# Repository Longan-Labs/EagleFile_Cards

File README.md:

# EagleFile_Cards
Eagle for All the Cards

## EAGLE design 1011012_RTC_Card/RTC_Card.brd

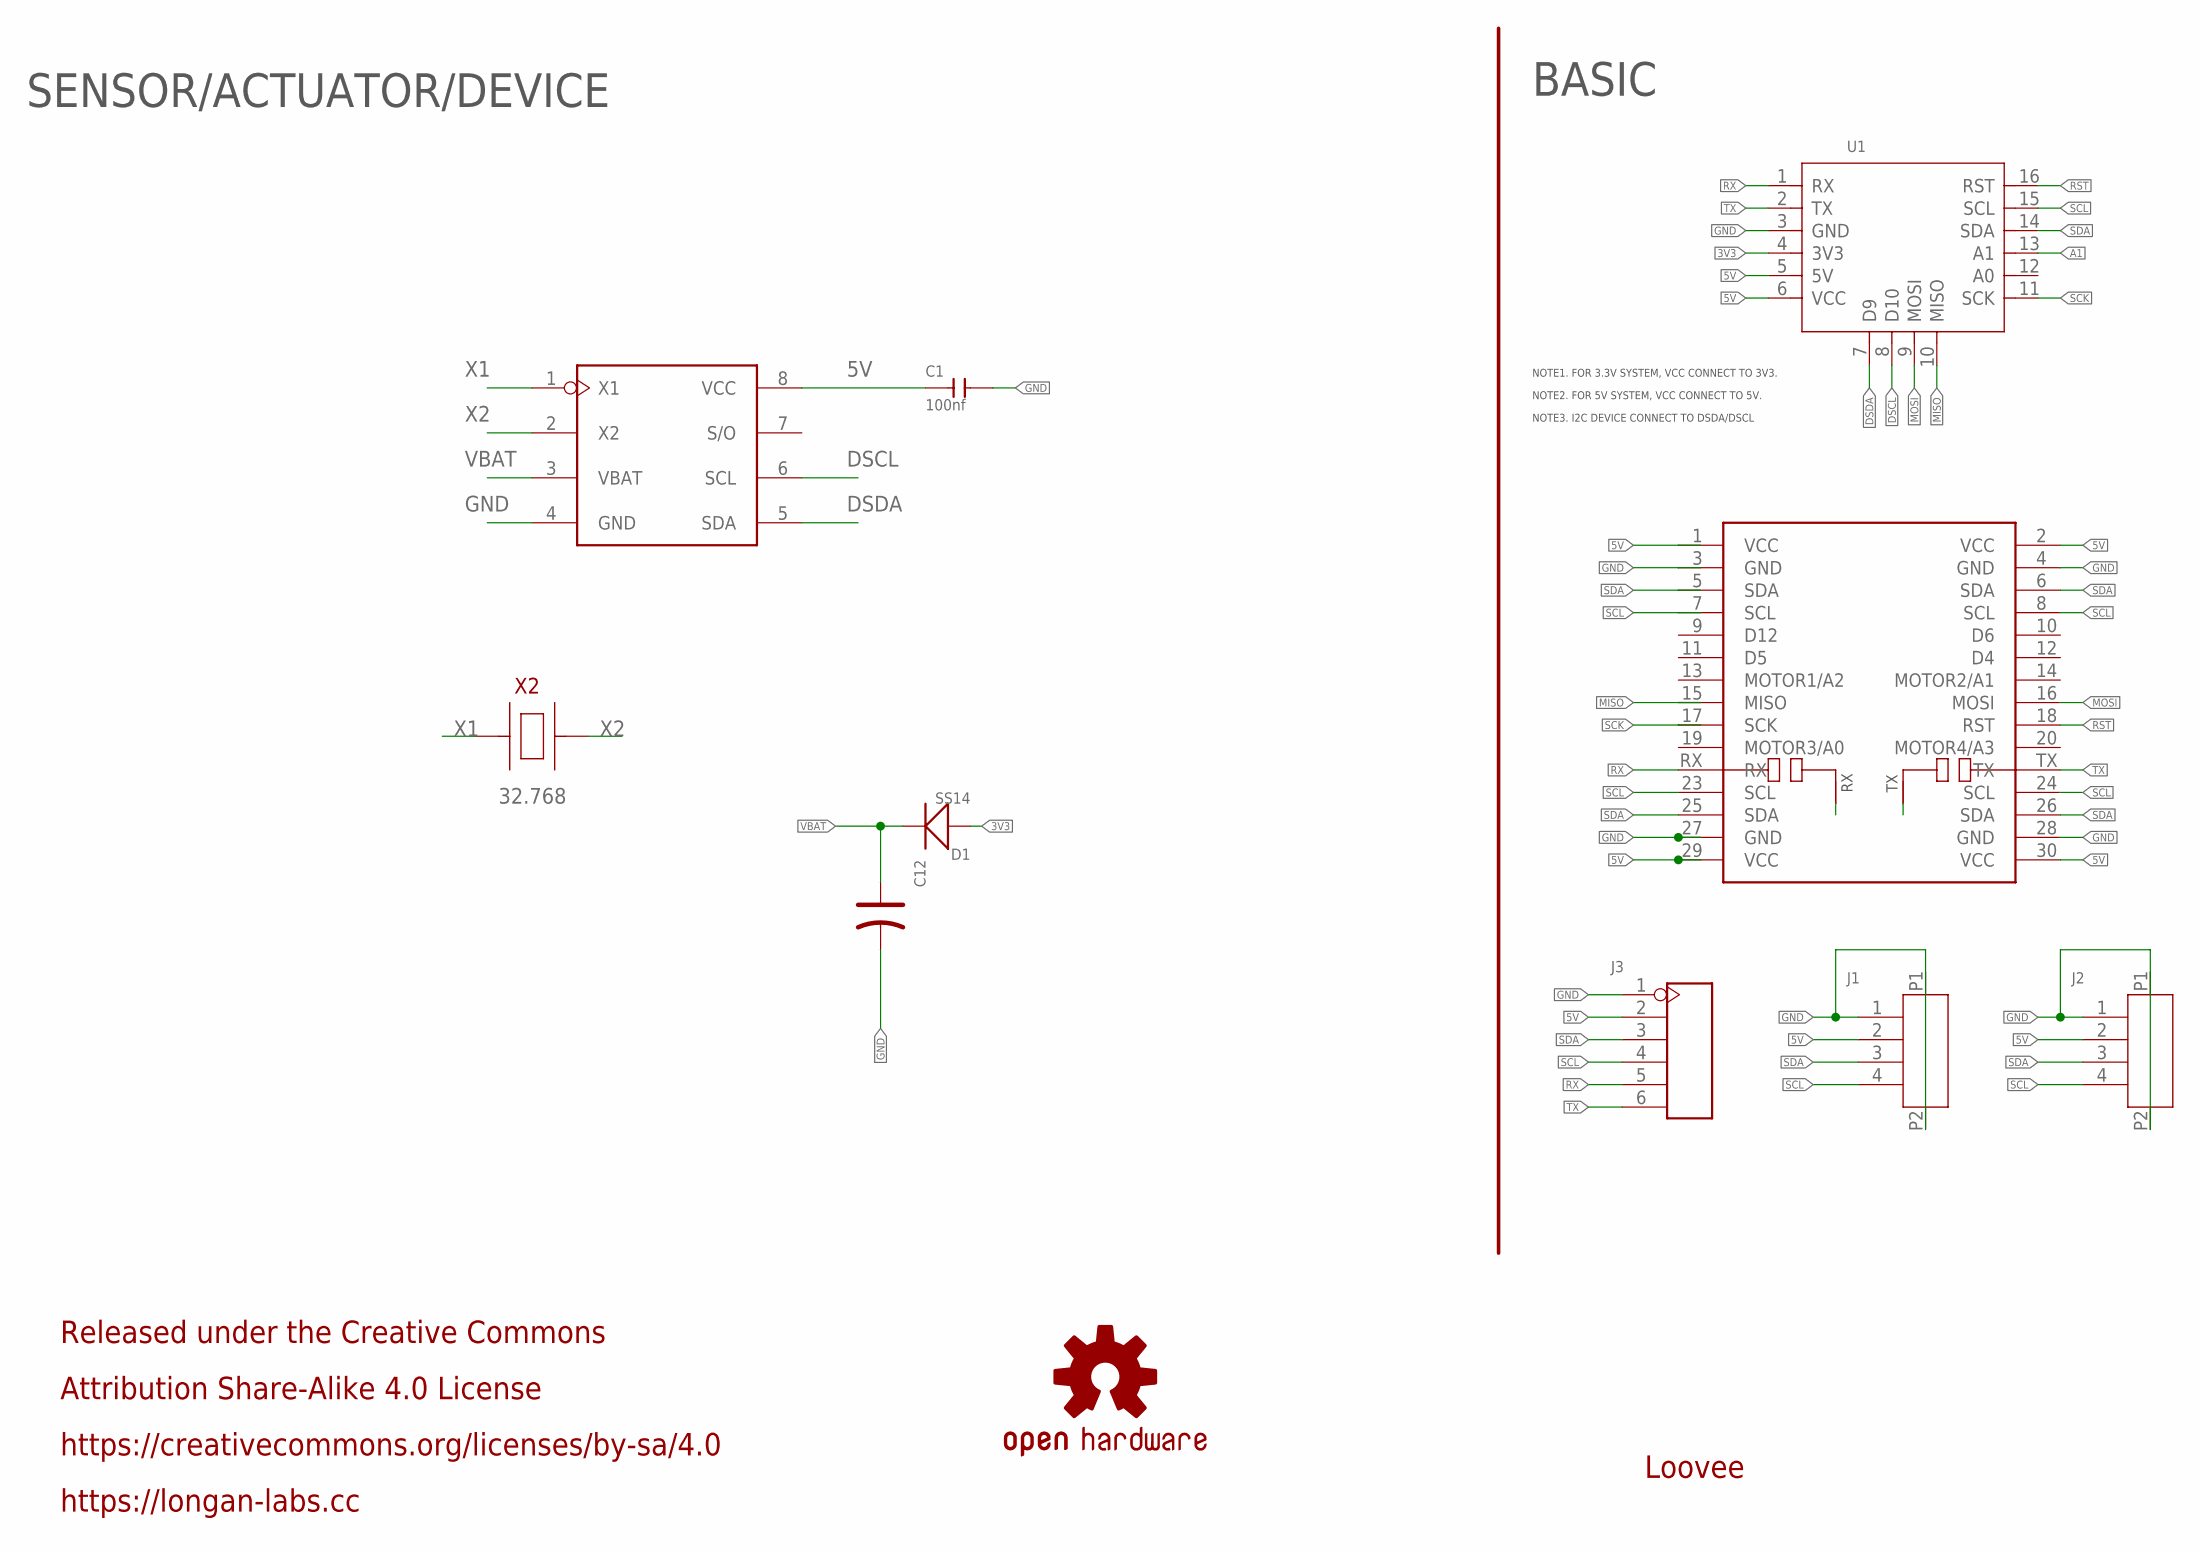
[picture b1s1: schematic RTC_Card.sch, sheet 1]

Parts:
C1: 100nf; C0603
C12: CAP-POLAR-CS-ME-414TA; SC-2P-D4.8MM
D1: SS14; DO-214AC
J1, J2: HEADER-4P-1.0; 4P-1.0-90D
J3: HEADER-6P-55/35MIL; H6-2.54
LOGO2: OSHW-LOGOS; OSHW-LOGO-S
MOUDLE2: MOUDLE-CARDS-UART'BOARD'; MOUDLE-2X15P-UART
U1: MOUDLE-CARDS; 16P-2.0-CARDS
U2: DS1307; SO08
X2: 32768; 2P-3215

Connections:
3V3: D1.1 (+), U1.4 (3V3)
5V: C1.1, J1.2, J2.2, J3.2, MOUDLE2.1 (VCC), MOUDLE2.2 (VCC), MOUDLE2.29 (VCC), MOUDLE2.30 (VCC), U1.5 (5V), U1.6 (VCC), U2.8 (VCC)
A1: U1.13 (A1)
DSCL: U1.8 (D10), U2.6 (SCL)
DSDA: U1.7 (D9), U2.5 (SDA)
GND: C1.2, C12.2 (-), J1.1, J1.P1, J1.P2, J2.1, J2.P1, J2.P2, J3.1, MOUDLE2.3 (GND), MOUDLE2.4 (GND), MOUDLE2.27 (GND), MOUDLE2.28 (GND), U1.3 (GND), U2.4 (GND)
MISO: MOUDLE2.15 (MISO), U1.10 (MISO)
MOSI: MOUDLE2.16 (MOSI), U1.9 (MOSI)
unnamed: MOUDLE2.RX/N1 (RX/N), MOUDLE2.RX/N2 (RX/N)
unnamed: MOUDLE2.TX/N1 (TX/N), MOUDLE2.TX/N2 (TX/N)
RST: MOUDLE2.18 (RST), U1.16 (RST)
RX: J3.5, MOUDLE2.RX, U1.1 (RX)
SCK: MOUDLE2.17 (SCK), U1.11 (SCK)
SCL: J1.4, J2.4, J3.4, MOUDLE2.7 (SCL), MOUDLE2.8 (SCL), MOUDLE2.23 (SCL), MOUDLE2.24 (SCL), U1.15 (SCL)
SDA: J1.3, J2.3, J3.3, MOUDLE2.5 (SDA), MOUDLE2.6 (SDA), MOUDLE2.25 (SDA), MOUDLE2.26 (SDA), U1.14 (SDA)
TX: J3.6, MOUDLE2.TX, U1.2 (TX)
VBAT: C12.1 (+), D1.2 (-), U2.3 (VBAT)
X1: U2.1 (X1), X2.X1
X2: U2.2 (X2), X2.X2

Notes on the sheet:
BASIC
Loovee
NOTE1. FOR 3.3V SYSTEM, VCC CONNECT TO 3V3.
NOTE2. FOR 5V SYSTEM, VCC CONNECT TO 5V.
NOTE3. I2C DEVICE CONNECT TO DSDA/DSCL
SENSOR/ACTUATOR/DEVICE
Released under the Creative Commons
Attribution Share-Alike 4.0 License
https://creativecommons.org/licenses/by-sa/4.0
https://longan-labs.cc
32.768

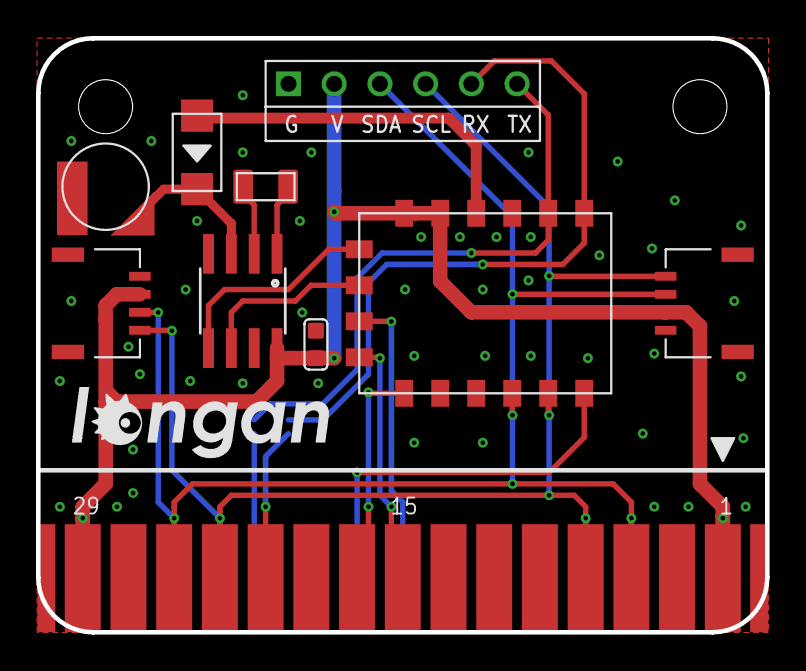
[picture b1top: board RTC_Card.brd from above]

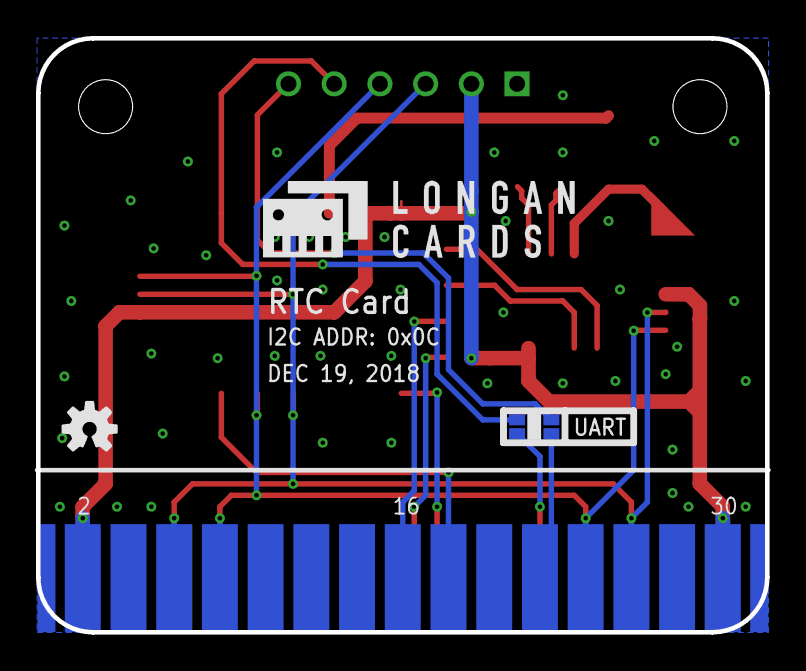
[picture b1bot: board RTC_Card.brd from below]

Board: 2 copper layers, 40.5 x 33.0 mm, 13 parts (2 on the bottom side), 18 nets.

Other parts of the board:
U$1: LONGAN-CARDS-MIDDLE
U$2: LONGAN-SILK-SMALLER

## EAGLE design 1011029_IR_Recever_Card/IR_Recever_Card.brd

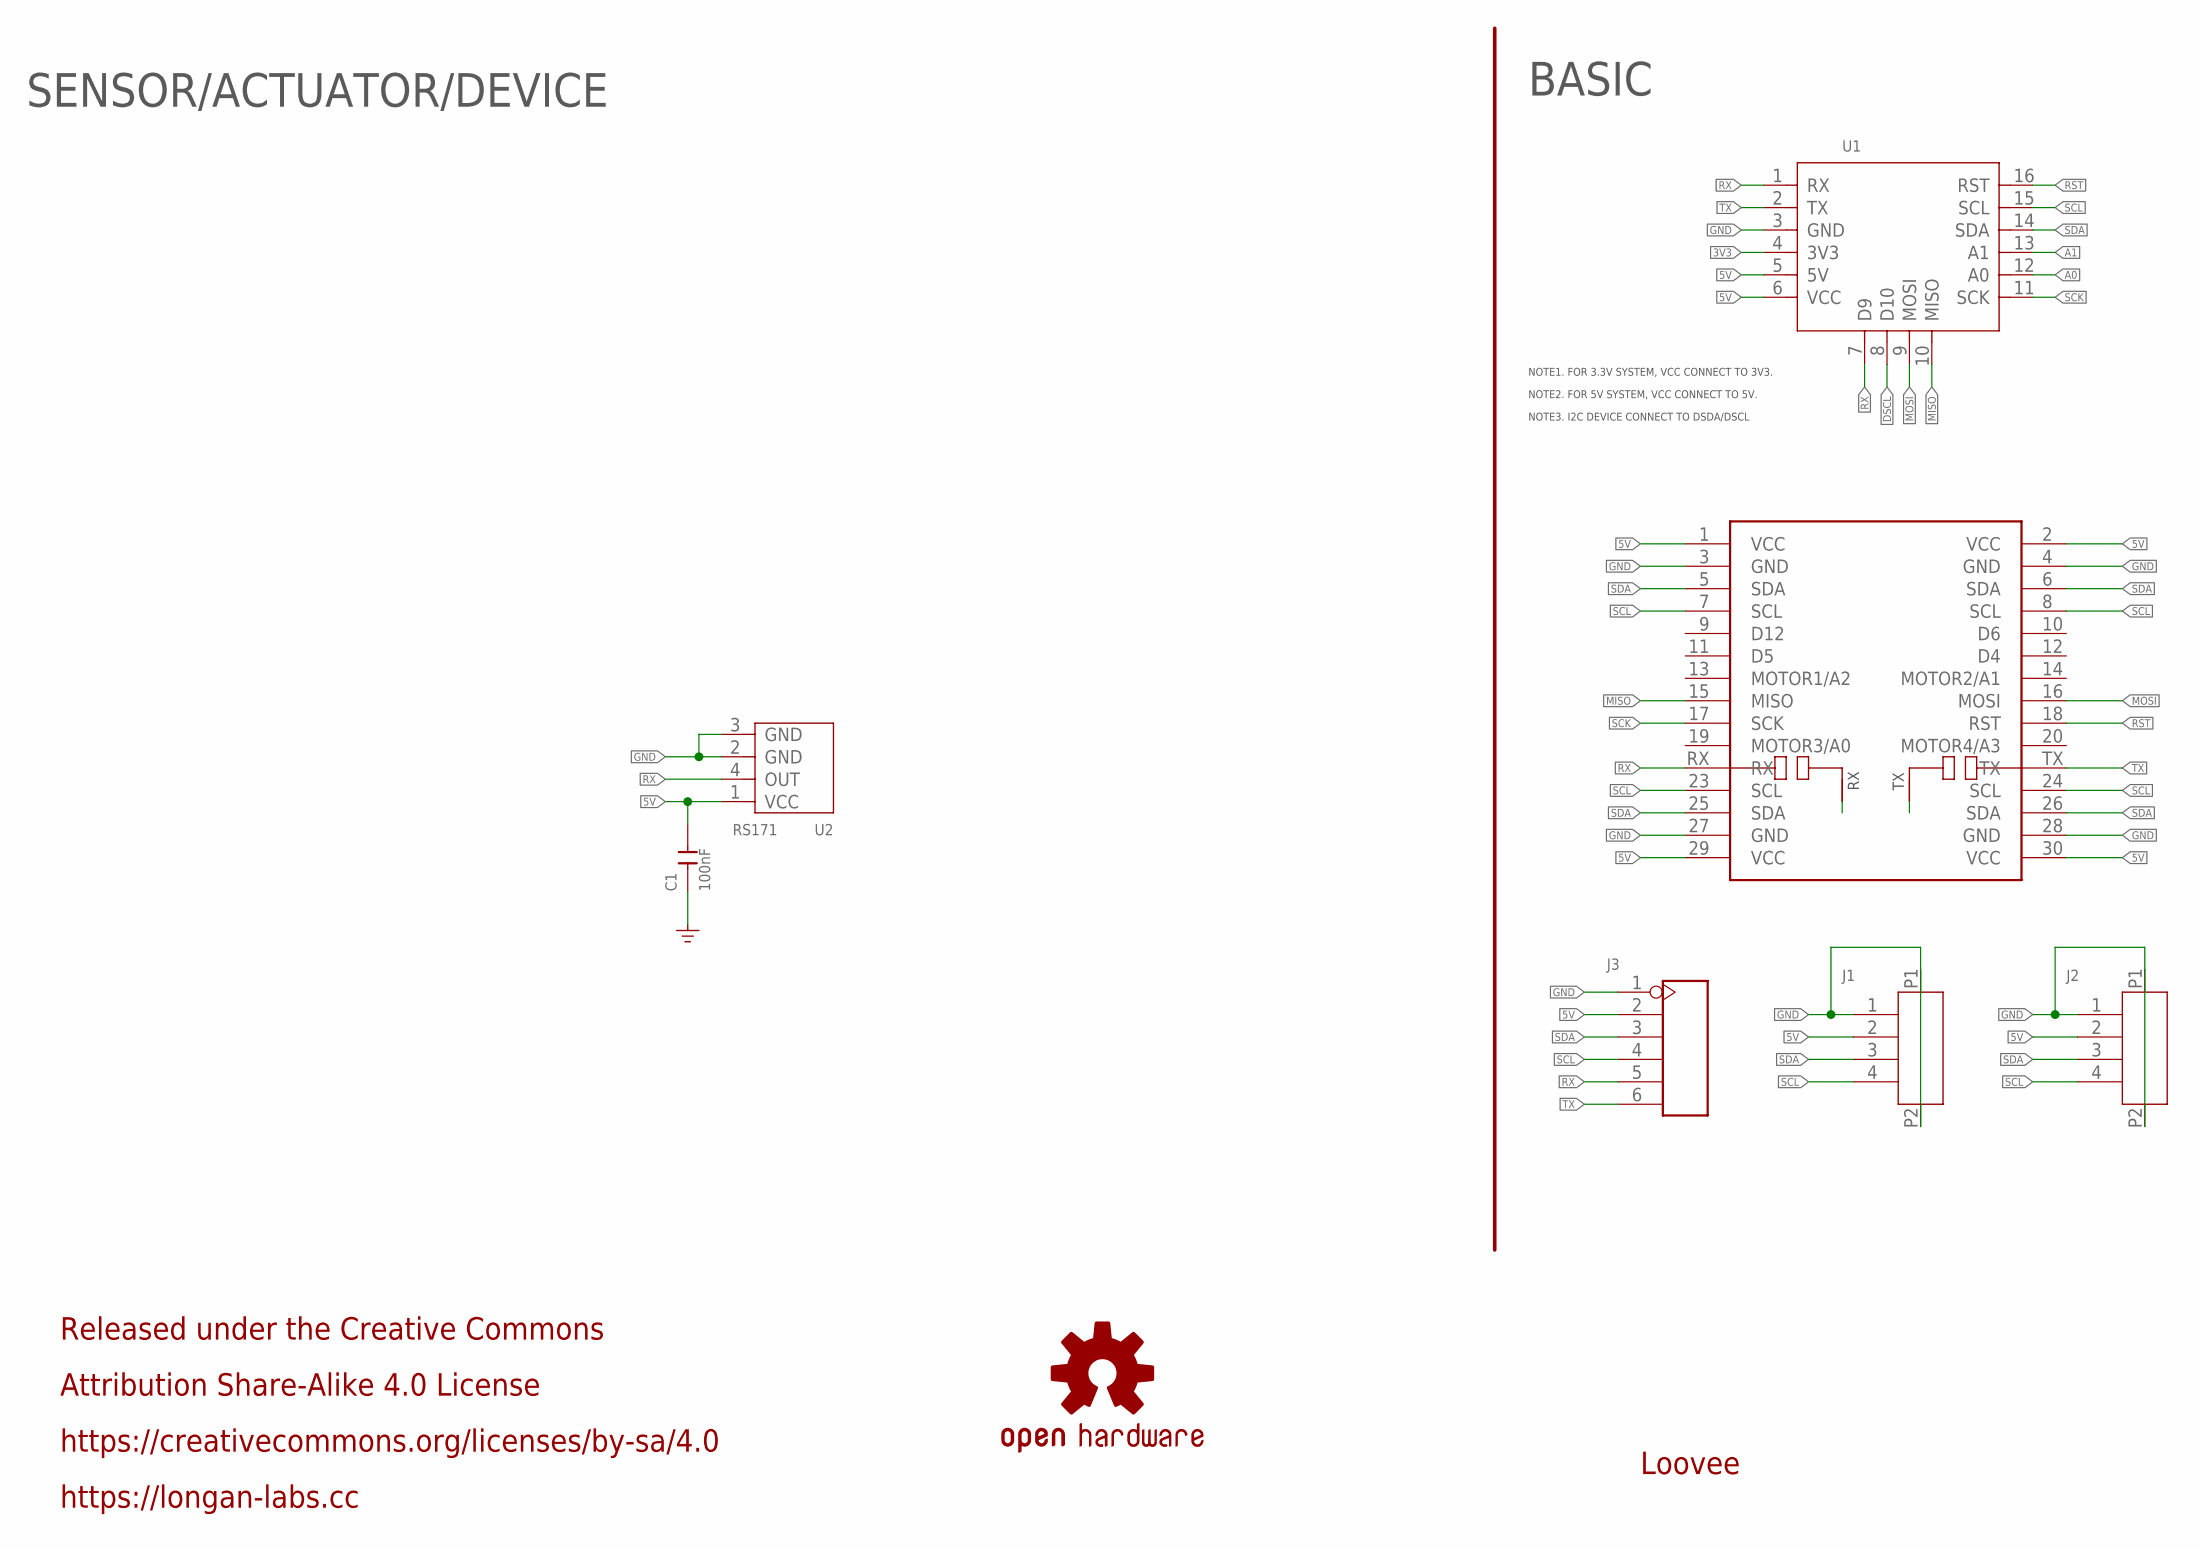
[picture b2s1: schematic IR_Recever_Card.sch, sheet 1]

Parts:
C1: 100nF; C0603
J1, J2: HEADER-4P-1.0; 4P-1.0-90D
J3: HEADER-6P-55/35MIL; H6-2.54
LOGO2: OSHW-LOGOS; OSHW-LOGO-S
MOUDLE1: MOUDLE-CARDS-UART'BOARD'; MOUDLE-2X15P-UART
U1: MOUDLE-CARDS; 16P-2.0-CARDS
U2: RS171; 4P-SMD-L7.6*W5.75MM

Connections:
3V3: U1.4 (3V3)
5V: C1.2, J1.2, J2.2, J3.2, MOUDLE1.1 (VCC), MOUDLE1.2 (VCC), MOUDLE1.29 (VCC), MOUDLE1.30 (VCC), U1.5 (5V), U1.6 (VCC), U2.1 (VCC)
A0: U1.12 (A0)
A1: U1.13 (A1)
DSCL: U1.8 (D10)
GND: C1.1, J1.1, J1.P1, J1.P2, J2.1, J2.P1, J2.P2, J3.1, MOUDLE1.3 (GND), MOUDLE1.4 (GND), MOUDLE1.27 (GND), MOUDLE1.28 (GND), U1.3 (GND), U2.2 (GND), U2.3 (GND)
MISO: MOUDLE1.15 (MISO), U1.10 (MISO)
MOSI: MOUDLE1.16 (MOSI), U1.9 (MOSI)
unnamed: MOUDLE1.RX/N1 (RX/N), MOUDLE1.RX/N2 (RX/N)
unnamed: MOUDLE1.TX/N1 (TX/N), MOUDLE1.TX/N2 (TX/N)
RST: MOUDLE1.18 (RST), U1.16 (RST)
RX: J3.5, MOUDLE1.RX, U1.1 (RX), U1.7 (D9), U2.4 (OUT)
SCK: MOUDLE1.17 (SCK), U1.11 (SCK)
SCL: J1.4, J2.4, J3.4, MOUDLE1.7 (SCL), MOUDLE1.8 (SCL), MOUDLE1.23 (SCL), MOUDLE1.24 (SCL), U1.15 (SCL)
SDA: J1.3, J2.3, J3.3, MOUDLE1.5 (SDA), MOUDLE1.6 (SDA), MOUDLE1.25 (SDA), MOUDLE1.26 (SDA), U1.14 (SDA)
TX: J3.6, MOUDLE1.TX, U1.2 (TX)

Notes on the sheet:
BASIC
Loovee
NOTE1. FOR 3.3V SYSTEM, VCC CONNECT TO 3V3.
NOTE2. FOR 5V SYSTEM, VCC CONNECT TO 5V.
NOTE3. I2C DEVICE CONNECT TO DSDA/DSCL
SENSOR/ACTUATOR/DEVICE
Released under the Creative Commons
Attribution Share-Alike 4.0 License
https://creativecommons.org/licenses/by-sa/4.0
https://longan-labs.cc

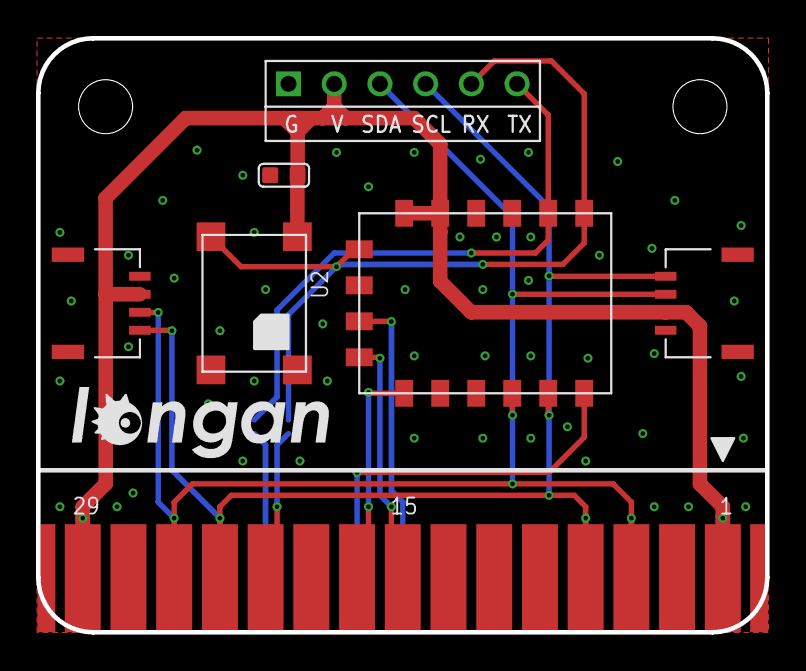
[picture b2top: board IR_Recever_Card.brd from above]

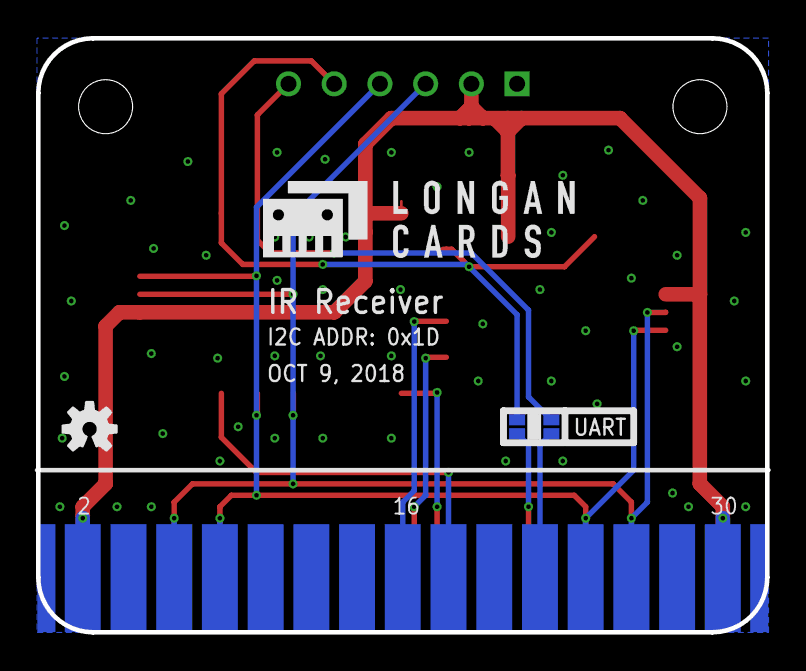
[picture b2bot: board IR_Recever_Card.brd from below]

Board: 2 copper layers, 40.5 x 33.0 mm, 10 parts (2 on the bottom side), 12 nets.

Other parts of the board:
U$1: LONGAN-CARDS-MIDDLE
U$2: LONGAN-SILK-SMALLER

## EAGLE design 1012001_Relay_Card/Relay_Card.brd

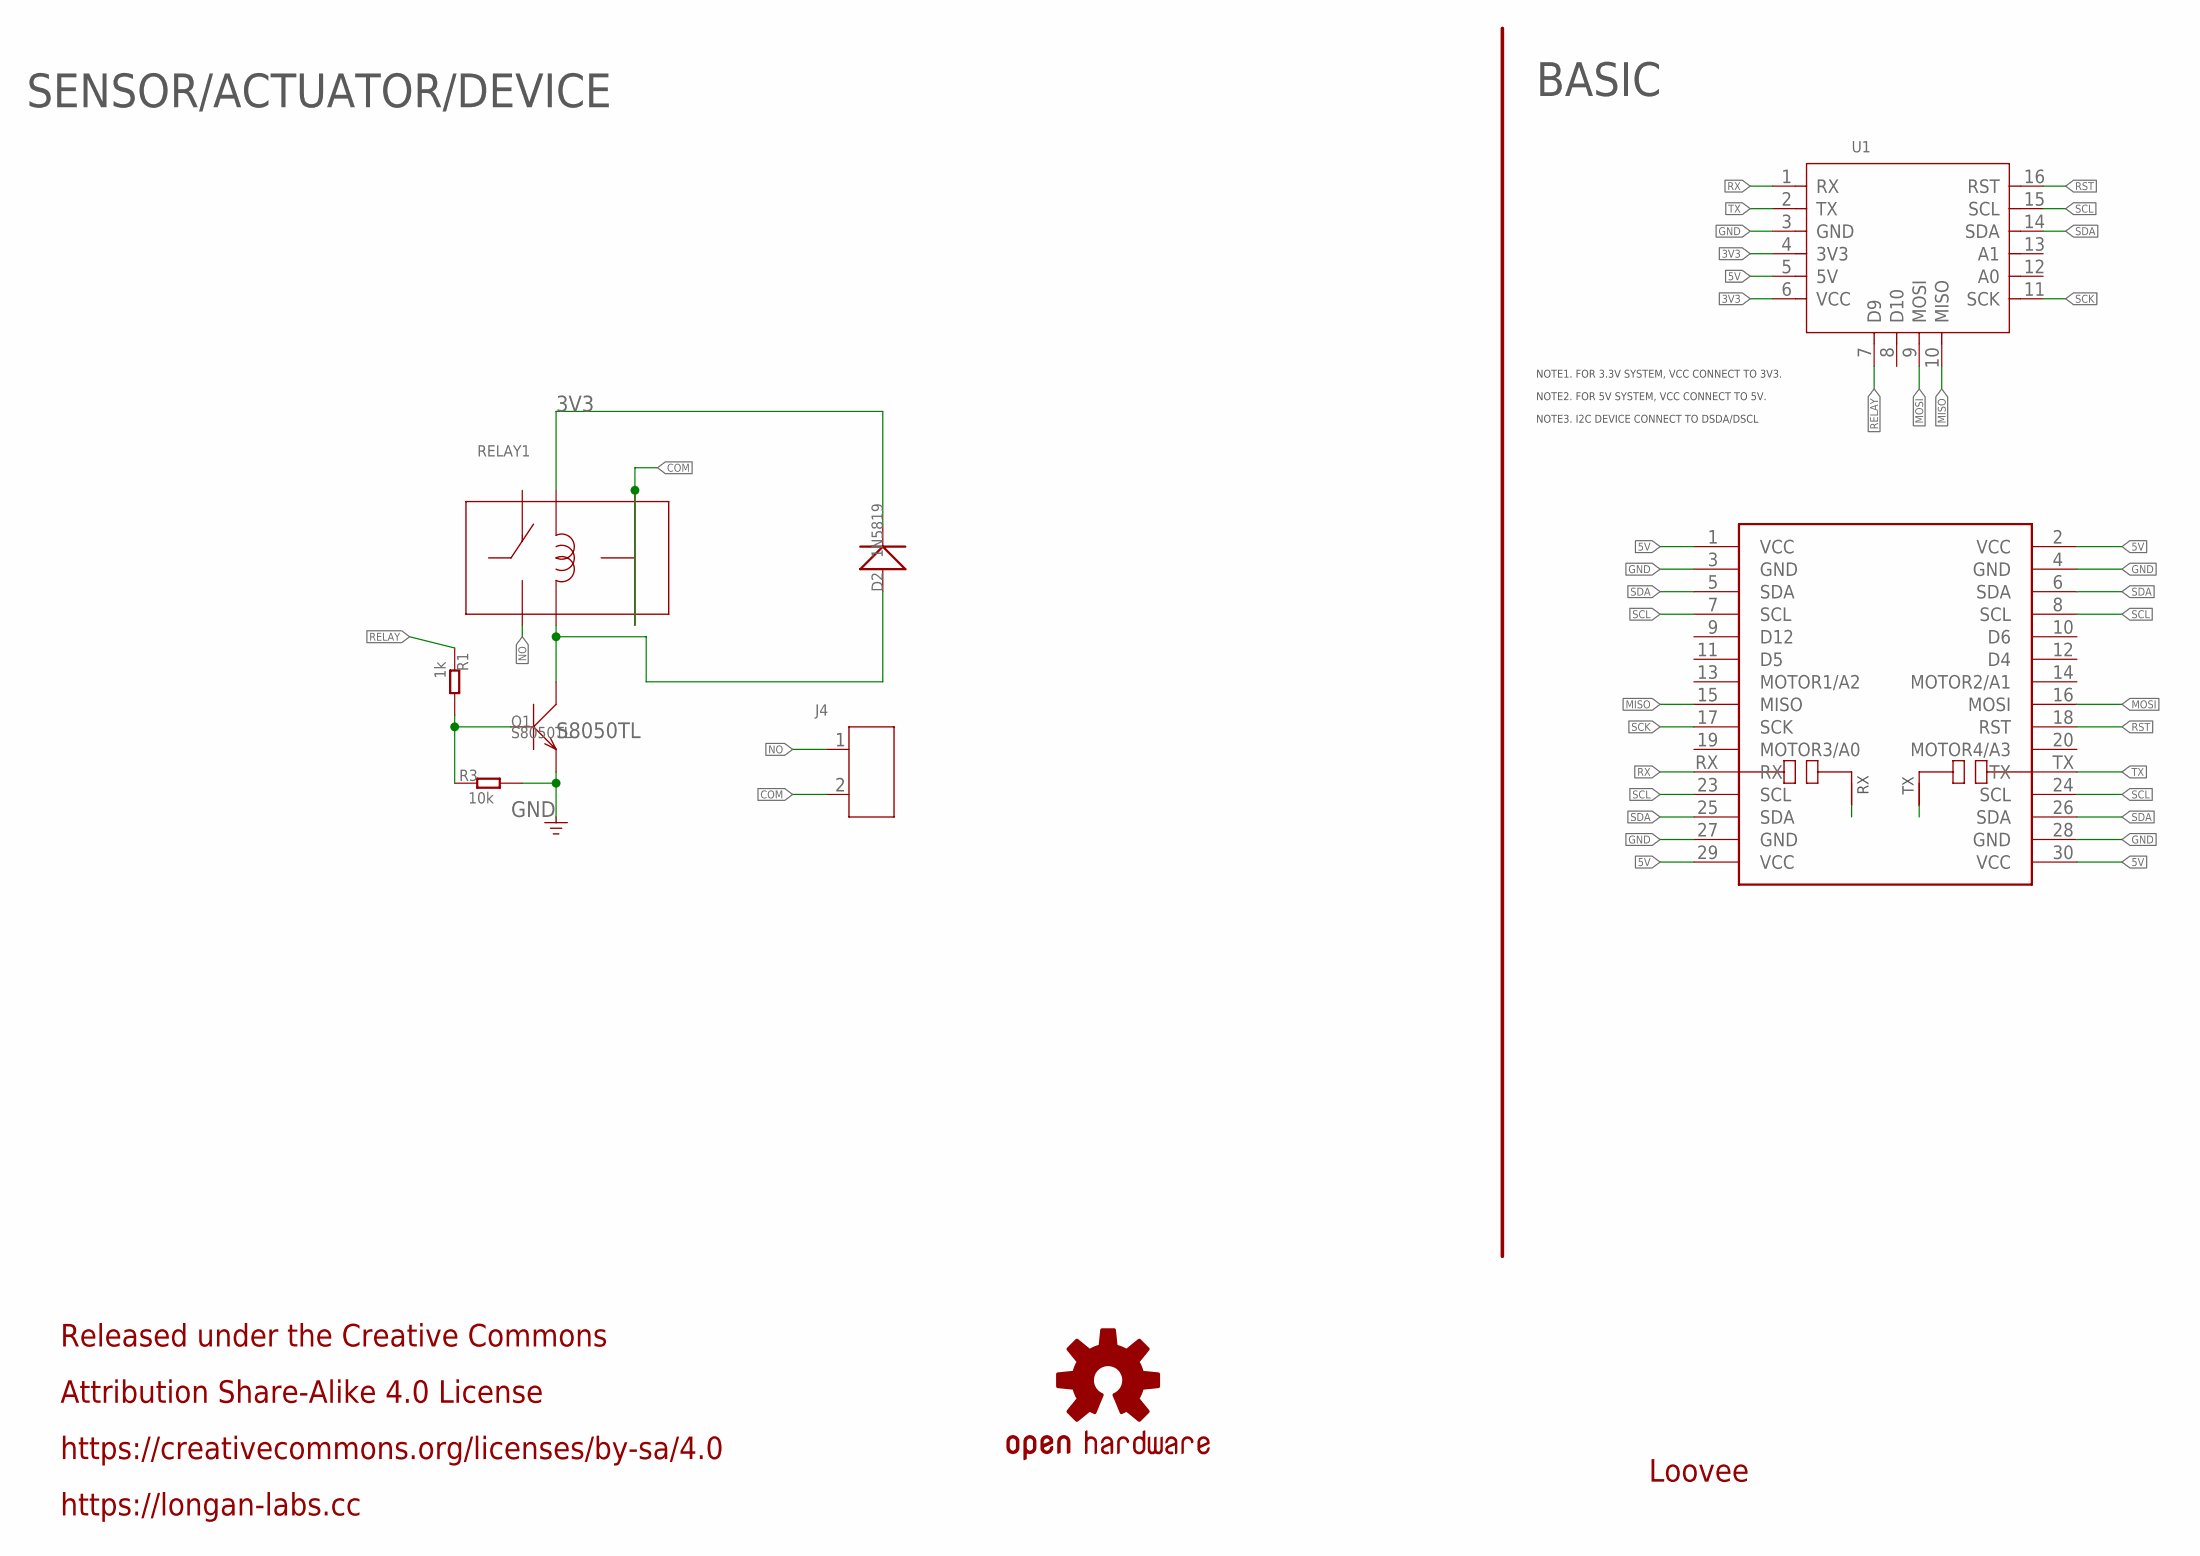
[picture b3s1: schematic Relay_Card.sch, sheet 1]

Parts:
D2: 1N5819; D2010
J4: SCREW-TERMINAL-2P'3.5'; H2-3.5-7.0X7.0MM
LOGO2: OSHW-LOGOS; OSHW-LOGO-S
MOUDLE2: MOUDLE-CARDS-UART'BOARD'; MOUDLE-2X15P-UART
Q1: S8050TL; SOT23
R1: 1k; R0603
R3: 10k; R0603
RELAY1: RELAY-HK4100F; 6P-15.5X10.5X11.8MM
U1: MOUDLE-CARDS; 16P-2.0-CARDS

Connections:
3V3: D2.-, RELAY1.2, U1.4 (3V3), U1.6 (VCC)
5V: MOUDLE2.1 (VCC), MOUDLE2.2 (VCC), MOUDLE2.29 (VCC), MOUDLE2.30 (VCC), U1.5 (5V)
COM: J4.2, RELAY1.3, RELAY1.6
GND: MOUDLE2.3 (GND), MOUDLE2.4 (GND), MOUDLE2.27 (GND), MOUDLE2.28 (GND), Q1.2 (E), R3.2, U1.3 (GND)
MISO: MOUDLE2.15 (MISO), U1.10 (MISO)
MOSI: MOUDLE2.16 (MOSI), U1.9 (MOSI)
unnamed: MOUDLE2.RX/N1 (RX/N), MOUDLE2.RX/N2 (RX/N)
unnamed: MOUDLE2.TX/N1 (TX/N), MOUDLE2.TX/N2 (TX/N)
unnamed: Q1.1 (B), R1.2, R3.1
unnamed: D2.+, Q1.3 (C), RELAY1.5
NO: J4.1, RELAY1.4
RELAY: R1.1, U1.7 (D9)
RST: MOUDLE2.18 (RST), U1.16 (RST)
RX: MOUDLE2.RX, U1.1 (RX)
SCK: MOUDLE2.17 (SCK), U1.11 (SCK)
SCL: MOUDLE2.7 (SCL), MOUDLE2.8 (SCL), MOUDLE2.23 (SCL), MOUDLE2.24 (SCL), U1.15 (SCL)
SDA: MOUDLE2.5 (SDA), MOUDLE2.6 (SDA), MOUDLE2.25 (SDA), MOUDLE2.26 (SDA), U1.14 (SDA)
TX: MOUDLE2.TX, U1.2 (TX)

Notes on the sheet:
BASIC
Loovee
NOTE1. FOR 3.3V SYSTEM, VCC CONNECT TO 3V3.
NOTE2. FOR 5V SYSTEM, VCC CONNECT TO 5V.
NOTE3. I2C DEVICE CONNECT TO DSDA/DSCL
SENSOR/ACTUATOR/DEVICE
Released under the Creative Commons
Attribution Share-Alike 4.0 License
https://creativecommons.org/licenses/by-sa/4.0
https://longan-labs.cc
S8050TL

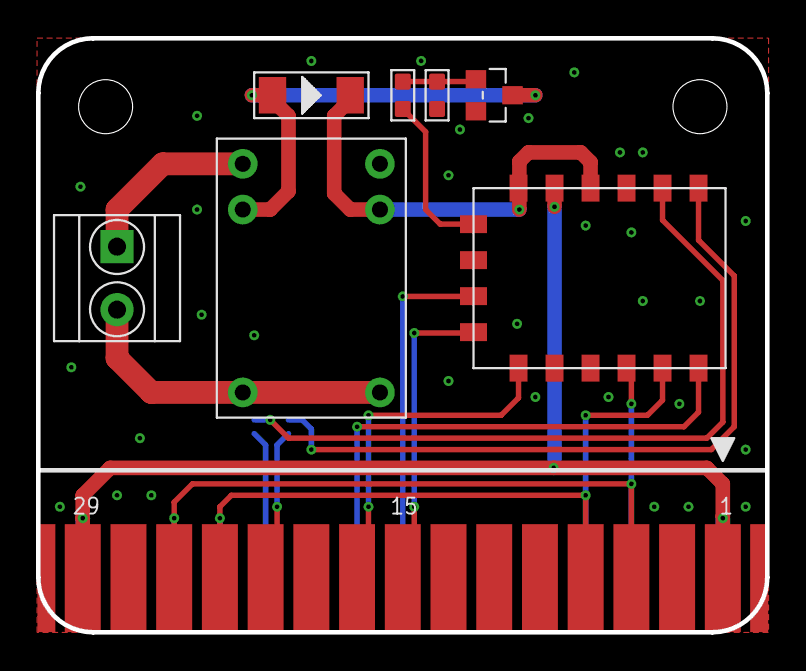
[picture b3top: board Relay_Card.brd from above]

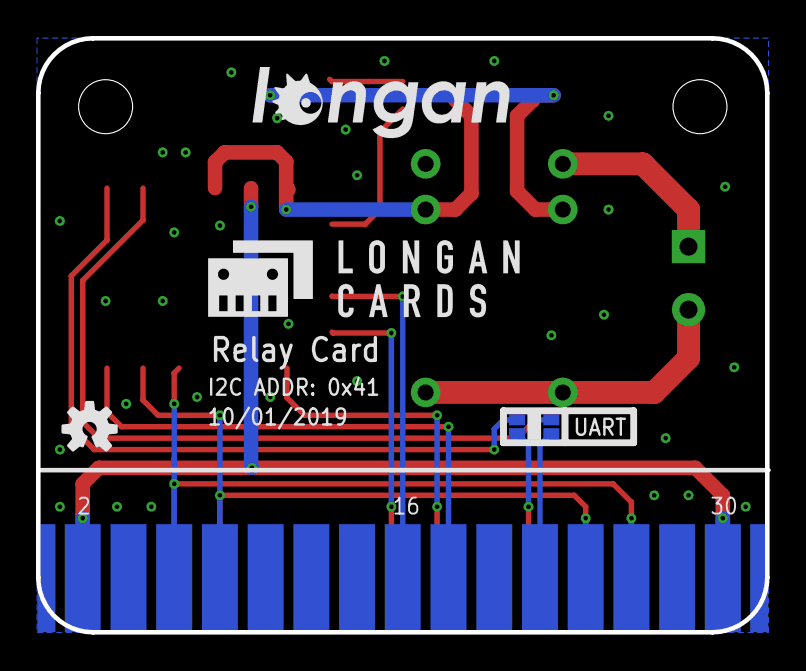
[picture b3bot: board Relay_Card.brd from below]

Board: 2 copper layers, 40.5 x 33.0 mm, 11 parts (3 on the bottom side), 18 nets.

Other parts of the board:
U$1: LONGAN-CARDS-MIDDLE
U$2: LONGAN-SILK-SMALLER

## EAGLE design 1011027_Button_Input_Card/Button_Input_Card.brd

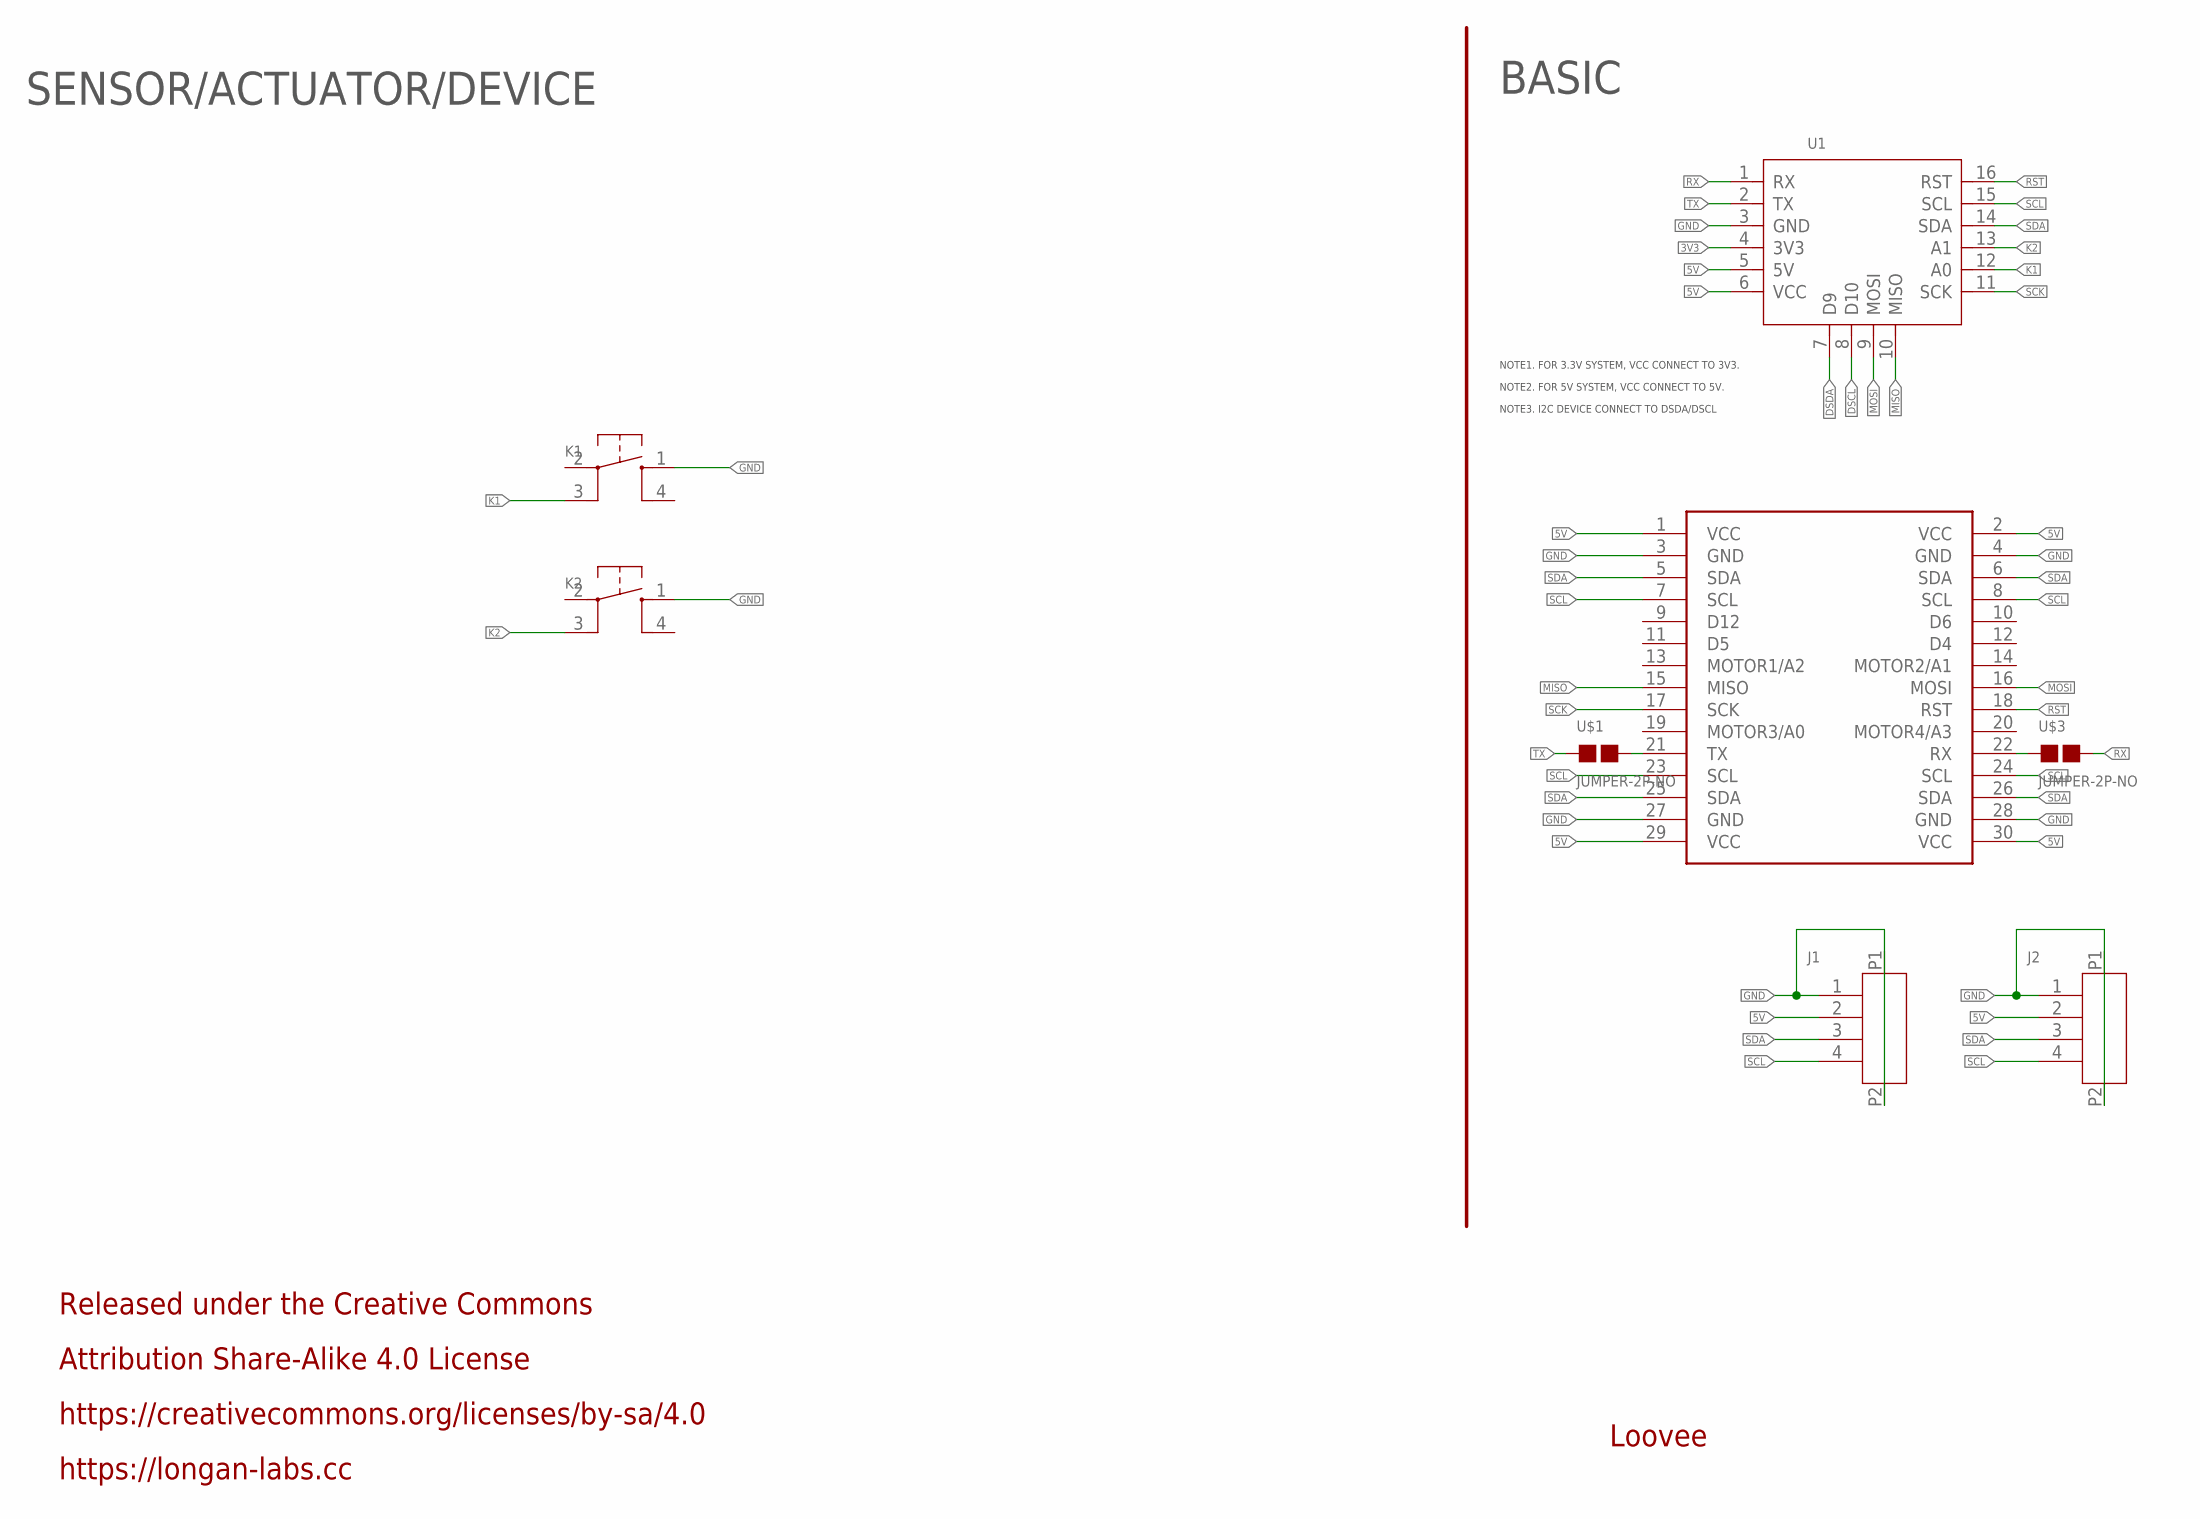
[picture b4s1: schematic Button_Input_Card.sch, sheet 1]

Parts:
J1, J2: HEADER-4P-1.0; 4P-1.0-90D
K1, K2: BUTTON-4P-SMT-TS-1103CW; SW4-SMD-5.0-12X12X7.5MM
MOUDLE1: MOUDLE-2X15P-2.54'BOARD'; MOUDLE-2X15P-2.54
U1: MOUDLE-CARDS; 16P-2.0-CARDS
U$1, U$3: JUMPER-2P-NO; 2P-SMD-NO

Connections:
3V3: U1.4 (3V3)
5V: J1.2, J2.2, MOUDLE1.1 (VCC), MOUDLE1.2 (VCC), MOUDLE1.29 (VCC), MOUDLE1.30 (VCC), U1.5 (5V), U1.6 (VCC)
DSCL: U1.8 (D10)
DSDA: U1.7 (D9)
GND: J1.1, J1.P1, J1.P2, J2.1, J2.P1, J2.P2, K1.1, K2.1, MOUDLE1.3 (GND), MOUDLE1.4 (GND), MOUDLE1.27 (GND), MOUDLE1.28 (GND), U1.3 (GND)
K1: K1.3, U1.12 (A0)
K2: K2.3, U1.13 (A1)
MISO: MOUDLE1.15 (MISO), U1.10 (MISO)
MOSI: MOUDLE1.16 (MOSI), U1.9 (MOSI)
unnamed: MOUDLE1.21 (TX), U$1.2
unnamed: MOUDLE1.22 (RX), U$3.1
RST: MOUDLE1.18 (RST), U1.16 (RST)
RX: U1.1 (RX), U$3.2
SCK: MOUDLE1.17 (SCK), U1.11 (SCK)
SCL: J1.4, J2.4, MOUDLE1.7 (SCL), MOUDLE1.8 (SCL), MOUDLE1.23 (SCL), MOUDLE1.24 (SCL), U1.15 (SCL)
SDA: J1.3, J2.3, MOUDLE1.5 (SDA), MOUDLE1.6 (SDA), MOUDLE1.25 (SDA), MOUDLE1.26 (SDA), U1.14 (SDA)
TX: U1.2 (TX), U$1.1

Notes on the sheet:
BASIC
Loovee
NOTE1. FOR 3.3V SYSTEM, VCC CONNECT TO 3V3.
NOTE2. FOR 5V SYSTEM, VCC CONNECT TO 5V.
NOTE3. I2C DEVICE CONNECT TO DSDA/DSCL
SENSOR/ACTUATOR/DEVICE
Released under the Creative Commons
Attribution Share-Alike 4.0 License
https://creativecommons.org/licenses/by-sa/4.0
https://longan-labs.cc

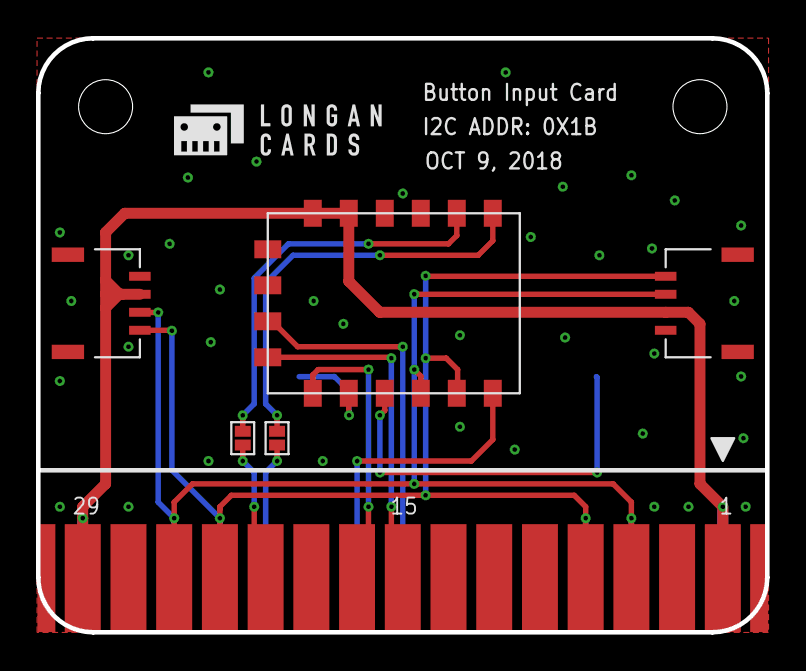
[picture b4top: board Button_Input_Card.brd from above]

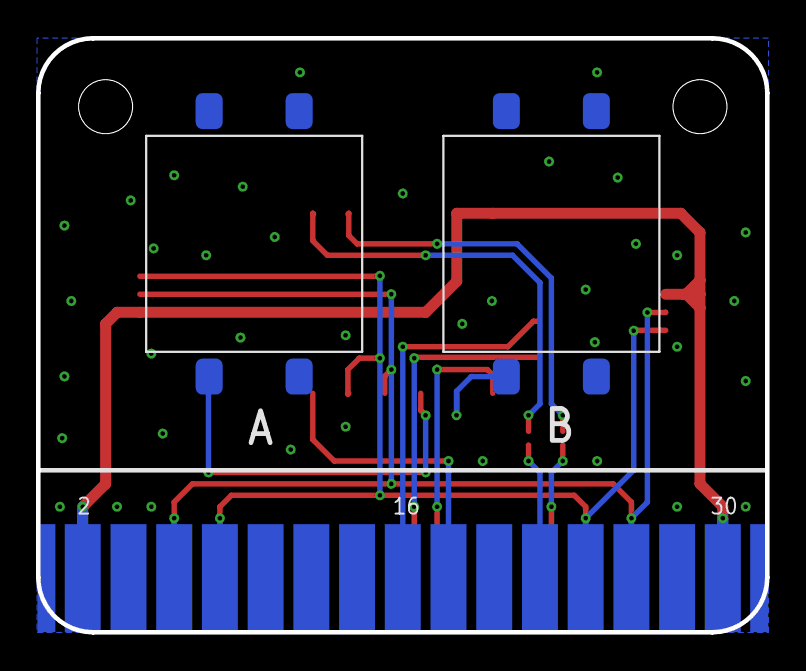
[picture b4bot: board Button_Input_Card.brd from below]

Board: 2 copper layers, 40.5 x 33.0 mm, 9 parts (2 on the bottom side), 14 nets.

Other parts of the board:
U$2: LONGAN-CARDS-SMALL

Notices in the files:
parts and their libraries:
SparkFun-Aesthetics: Licensing: CC v3.0 Share-Alike You are welcome to use this library for commercial purposes.
